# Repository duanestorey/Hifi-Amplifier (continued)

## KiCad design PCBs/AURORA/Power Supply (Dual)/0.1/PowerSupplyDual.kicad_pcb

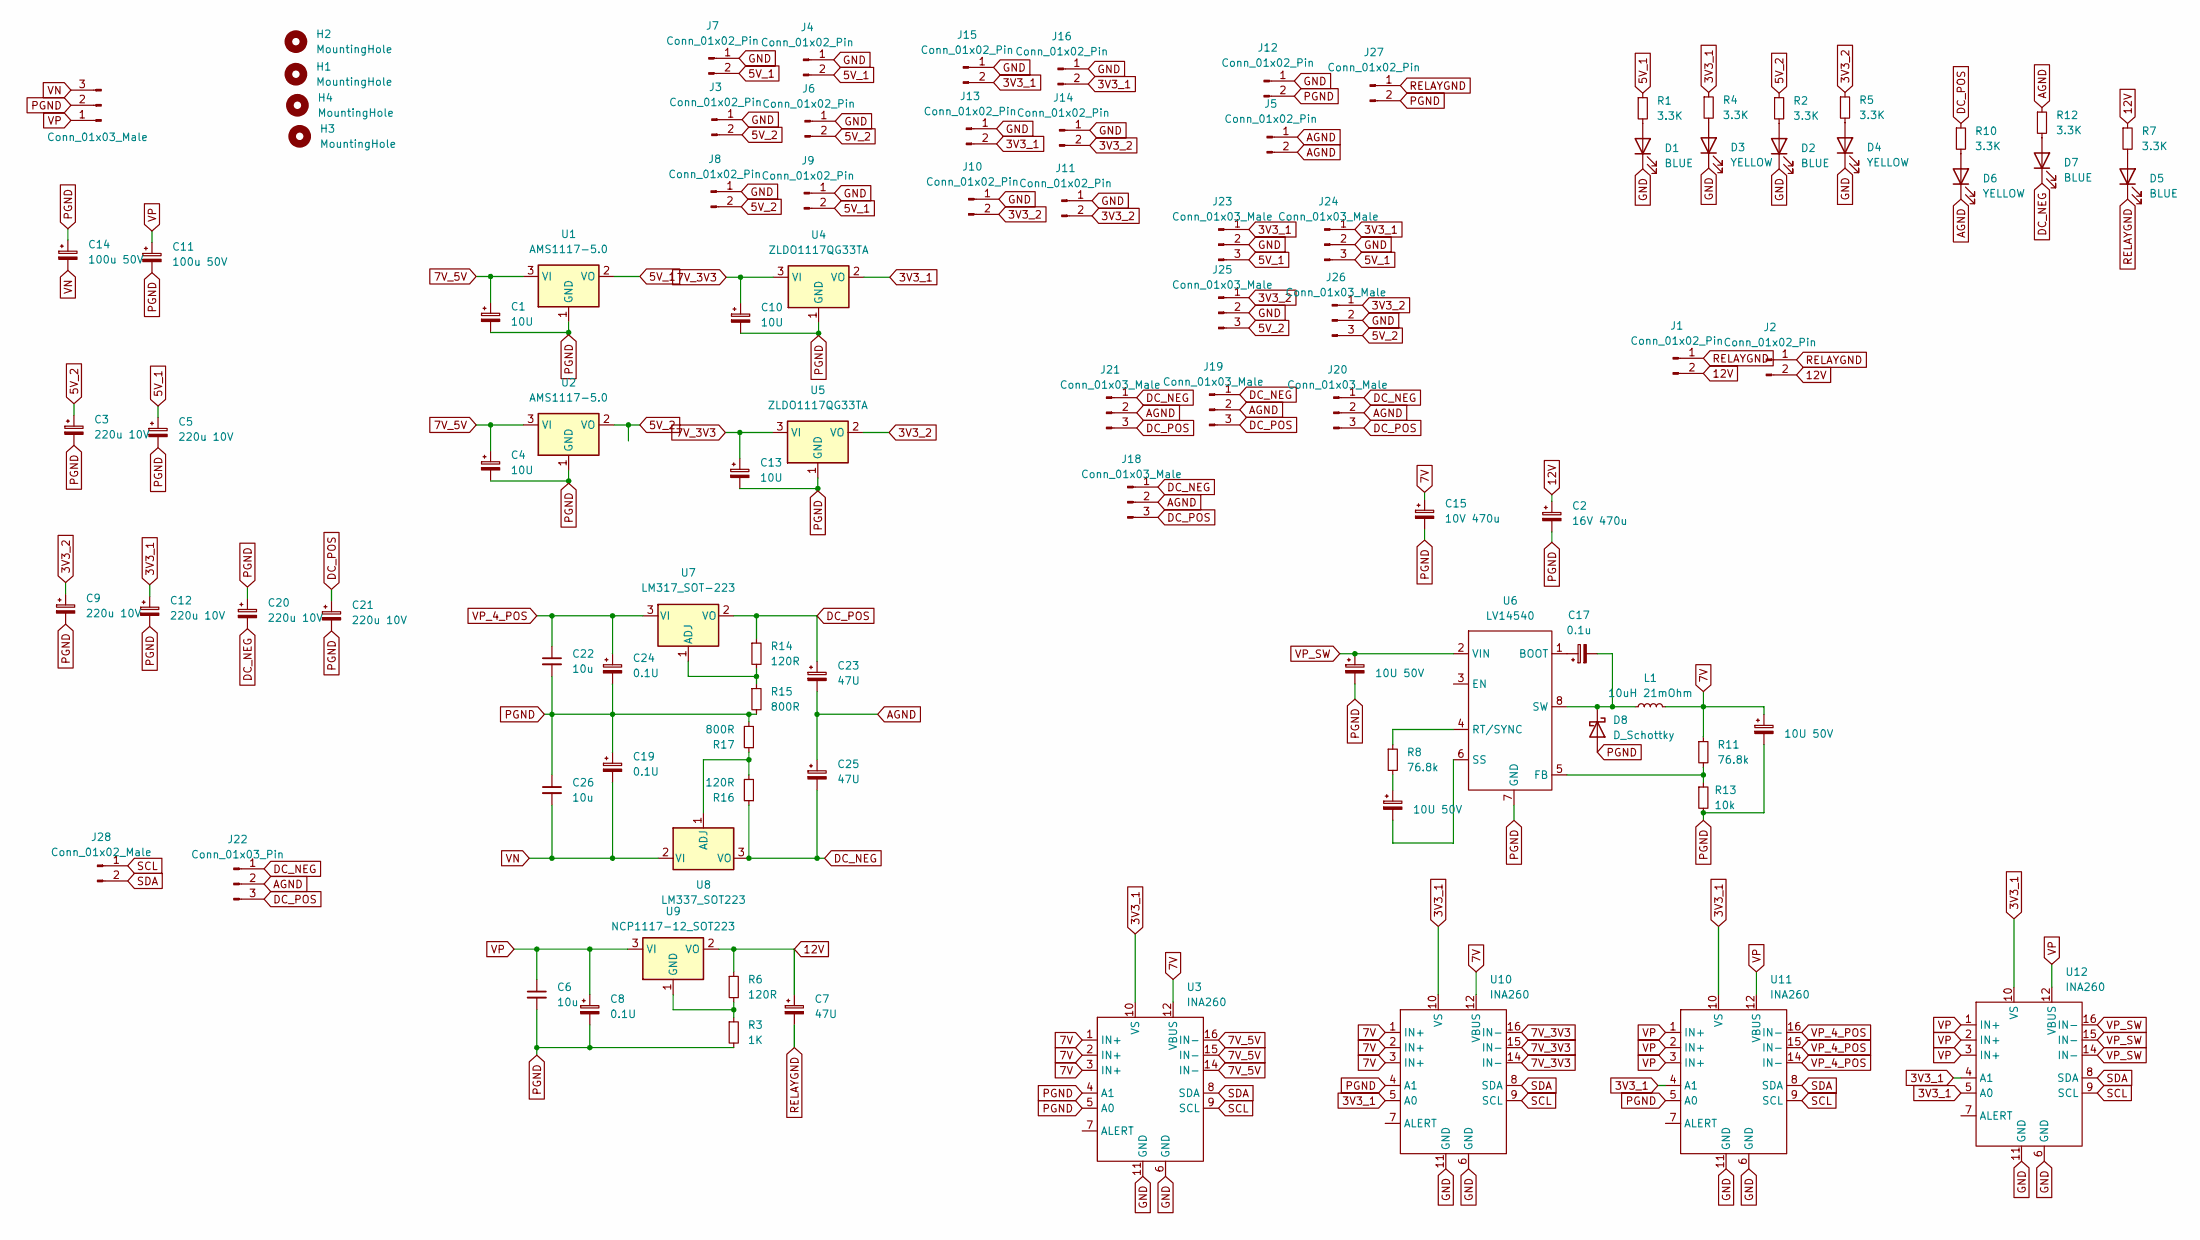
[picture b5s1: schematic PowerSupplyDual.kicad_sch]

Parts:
C1, C4, C10, C13: 10U; C_1206_3216Metric_Pad1.33x1.80mm_HandSolder
C2: 16V 470u; CP_Radial_D8.0mm_P3.50mm
C3, C5, C9, C12, C20, C21: 220u 10V; CP_Radial_D6.3mm_P2.50mm
C6, C22, C26: 10u; C_1206_3216Metric_Pad1.33x1.80mm_HandSolder
C7, C23, C25: 47U; C_1206_3216Metric_Pad1.33x1.80mm_HandSolder
C8, C19, C24: 0.1U; C_0603_1608Metric_Pad1.08x0.95mm_HandSolder
C11, C14: 100u 50V; CP_Radial_D8.0mm_P3.50mm
C15: 10V 470u; CP_Radial_D8.0mm_P3.50mm
C16, C18, C27: 10U 50V; C_1206_3216Metric_Pad1.33x1.80mm_HandSolder
C17: 0.1u; C_0805_2012Metric_Pad1.18x1.45mm_HandSolder
D1, D2, D5, D7: BLUE; LED_0805_2012Metric_Pad1.15x1.40mm_HandSolder
D3, D4, D6: YELLOW; LED_0805_2012Metric_Pad1.15x1.40mm_HandSolder
D8: D_Schottky; D_MELF
H1, H2, H3, H4: MountingHole; MountingHole_3.2mm_M3
J1, J2, J3, J4, J5, J6, J7, J8, J9, J10, J11, J13, J14, J15, J16: Conn_01x02_Pin; JST_PH_B2B-PH-K_1x02_P2.00mm_Vertical
J12, J27: Conn_01x02_Pin; PinHeader_1x02_P2.54mm_Vertical
J17: Conn_01x03_Male; JST_VH_B3P-VH_1x03_P3.96mm_Vertical
J18, J19, J20, J21, J23, J24, J25, J26: Conn_01x03_Male; JST_PH_B3B-PH-K_1x03_P2.00mm_Vertical
J22: Conn_01x03_Pin; PinHeader_1x03_P2.54mm_Vertical
J28: Conn_01x02_Male; JST_PH_B2B-PH-K_1x02_P2.00mm_Vertical
L1: 10uH 21mOhm; L_Bourns_SRR1208_12.7x12.7mm
R1, R2, R4, R5, R7, R10, R12: 3.3K; R_0603_1608Metric_Pad0.98x0.95mm_HandSolder
R3: 1K; R_0603_1608Metric_Pad0.98x0.95mm_HandSolder
R6, R14, R16: 120R; R_0603_1608Metric_Pad0.98x0.95mm_HandSolder
R8, R11: 76.8k; R_0603_1608Metric_Pad0.98x0.95mm_HandSolder
R13: 10k; R_0603_1608Metric_Pad0.98x0.95mm_HandSolder
R15, R17: 800R; R_0603_1608Metric_Pad0.98x0.95mm_HandSolder
U1, U2: AMS1117-5.0; SOT-223-3_TabPin2
U3, U10, U11, U12: INA260; TSSOP-16_4.4x5mm_P0.65mm
U4, U5: ZLDO1117QG33TA; SOT-223-3_TabPin2
U6: LV14540; Texas_R-PDSO-G8_EP2.95x4.9mm_Mask2.4x3.1mm_ThermalVias
U7: LM317_SOT-223; SOT-223-3_TabPin2
U8: LM337_SOT223; SOT-223-3_TabPin2
U9: NCP1117-12_SOT223; SOT-223-3_TabPin2

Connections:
3V3_1: C12.1, J13.2, J15.2, J16.2, J23.1, J24.1, R4.1, U3.10 (VS), U4.2 (VO), U10.5 (A0), U10.10 (VS), U11.4 (A1), U11.10 (VS), U12.4 (A1), U12.5 (A0), U12.10 (VS)
3V3_2: C9.1, J10.2, J11.2, J14.2, J25.1, J26.1, R5.1, U5.2 (VO)
5V_1: C5.1, J4.2, J7.2, J9.2, J23.3, J24.3, R1.1, U1.2 (VO)
5V_2: C3.1, J3.2, J6.2, J8.2, J25.3, J26.3, R2.1, U2.2 (VO)
7V: C15.1, C18.1, L1.2, R11.1, U3.1 (IN+), U3.2 (IN+), U3.3 (IN+), U3.12 (VBUS), U10.1 (IN+), U10.2 (IN+), U10.3 (IN+), U10.12 (VBUS)
7V_3V3: C10.1, C13.1, U4.3 (VI), U5.3 (VI), U10.14 (IN-), U10.15 (IN-), U10.16 (IN-)
7V_5V: C1.1, C4.1, U1.3 (VI), U2.3 (VI), U3.14 (IN-), U3.15 (IN-), U3.16 (IN-)
12V: C2.1, C7.1, J1.2, J2.2, R6.1, R7.1, U9.2 (VO)
AGND: C23.2, C25.1, D6.1 (K), J5.1, J5.2, J18.2, J19.2, J20.2, J21.2, J22.2, R12.1
DC_NEG: C20.2, C25.2, D7.1 (K), J18.1, J19.1, J20.1, J21.1, J22.1, R16.1, U8.3 (VO)
DC_POS: C21.1, C23.1, J18.3, J19.3, J20.3, J21.3, J22.3, R10.1, R14.1, U7.2 (VO)
GND: D1.1 (K), D2.1 (K), D3.1 (K), D4.1 (K), J3.1, J4.1, J6.1, J7.1, J8.1, J9.1, J10.1, J11.1, J12.1, J13.1, J14.1, J15.1, J16.1, J23.2, J24.2, J25.2, J26.2, U3.6 (GND), U3.11 (GND), U10.6 (GND), U10.11 (GND), U11.6 (GND), U11.11 (GND), U12.6 (GND), U12.11 (GND)
unnamed: C27.1, R8.2
unnamed: D1.2 (A), R1.2
unnamed: D2.2 (A), R2.2
unnamed: D3.2 (A), R4.2
unnamed: D4.2 (A), R5.2
unnamed: D5.2 (A), R7.2
unnamed: D6.2 (A), R10.2
unnamed: D7.2 (A), R12.2
unnamed: C17.2, D8.1 (K), L1.1, U6.8 (SW)
unnamed: C17.1, U6.1 (BOOT)
unnamed: R11.2, R13.1, U6.5 (FB)
unnamed: R8.1, U6.4 (RT/SYNC)
unnamed: C27.2, U6.6 (SS)
unnamed: R14.2, R15.1, U7.1 (ADJ)
unnamed: R16.2, R17.1, U8.1 (ADJ)
unnamed: R3.1, R6.2, U9.1 (GND)
PGND: C1.2, C2.2, C3.2, C4.2, C5.2, C6.2, C8.2, C9.2, C10.2, C11.2, C12.2, C13.2, C14.1, C15.2, C16.2, C18.2, C19.1, C20.1, C21.2, C22.2, C24.2, C26.1, D8.2 (A), J12.2, J17.2, J27.2, R3.2, R13.2, R15.2, R17.2, U1.1 (GND), U2.1 (GND), U3.4 (A1), U3.5 (A0), U4.1 (GND), U5.1 (GND), U6.7 (GND), U10.4 (A1), U11.5 (A0)
RELAYGND: C7.2, D5.1 (K), J1.1, J2.1, J27.1
SCL: J28.1, U3.9 (SCL), U10.9 (SCL), U11.9 (SCL), U12.9 (SCL)
SDA: J28.2, U3.8 (SDA), U10.8 (SDA), U11.8 (SDA), U12.8 (SDA)
VN: C14.2, C19.2, C26.2, J17.3, U8.2 (VI)
VP: C6.1, C8.1, C11.1, J17.1, U9.3 (VI), U11.1 (IN+), U11.2 (IN+), U11.3 (IN+), U11.12 (VBUS), U12.1 (IN+), U12.2 (IN+), U12.3 (IN+), U12.12 (VBUS)
VP_4_POS: C22.1, C24.1, U7.3 (VI), U11.14 (IN-), U11.15 (IN-), U11.16 (IN-)
VP_SW: C16.1, U6.2 (VIN), U12.14 (IN-), U12.15 (IN-), U12.16 (IN-)

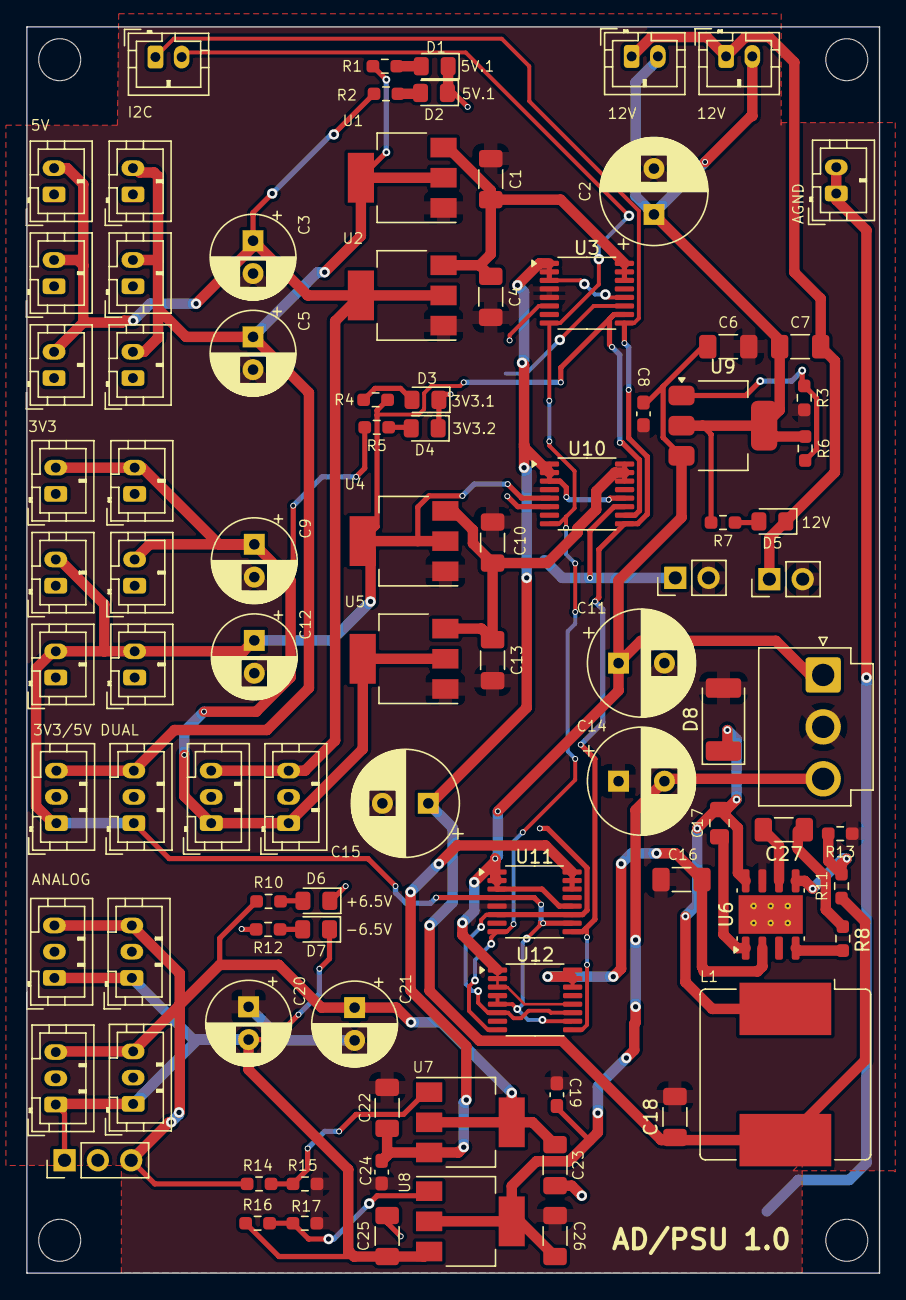
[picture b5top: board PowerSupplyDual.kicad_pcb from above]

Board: 2 copper layers, 65.0 x 95.0 mm, 96 parts (0 on the bottom side), 36 nets.

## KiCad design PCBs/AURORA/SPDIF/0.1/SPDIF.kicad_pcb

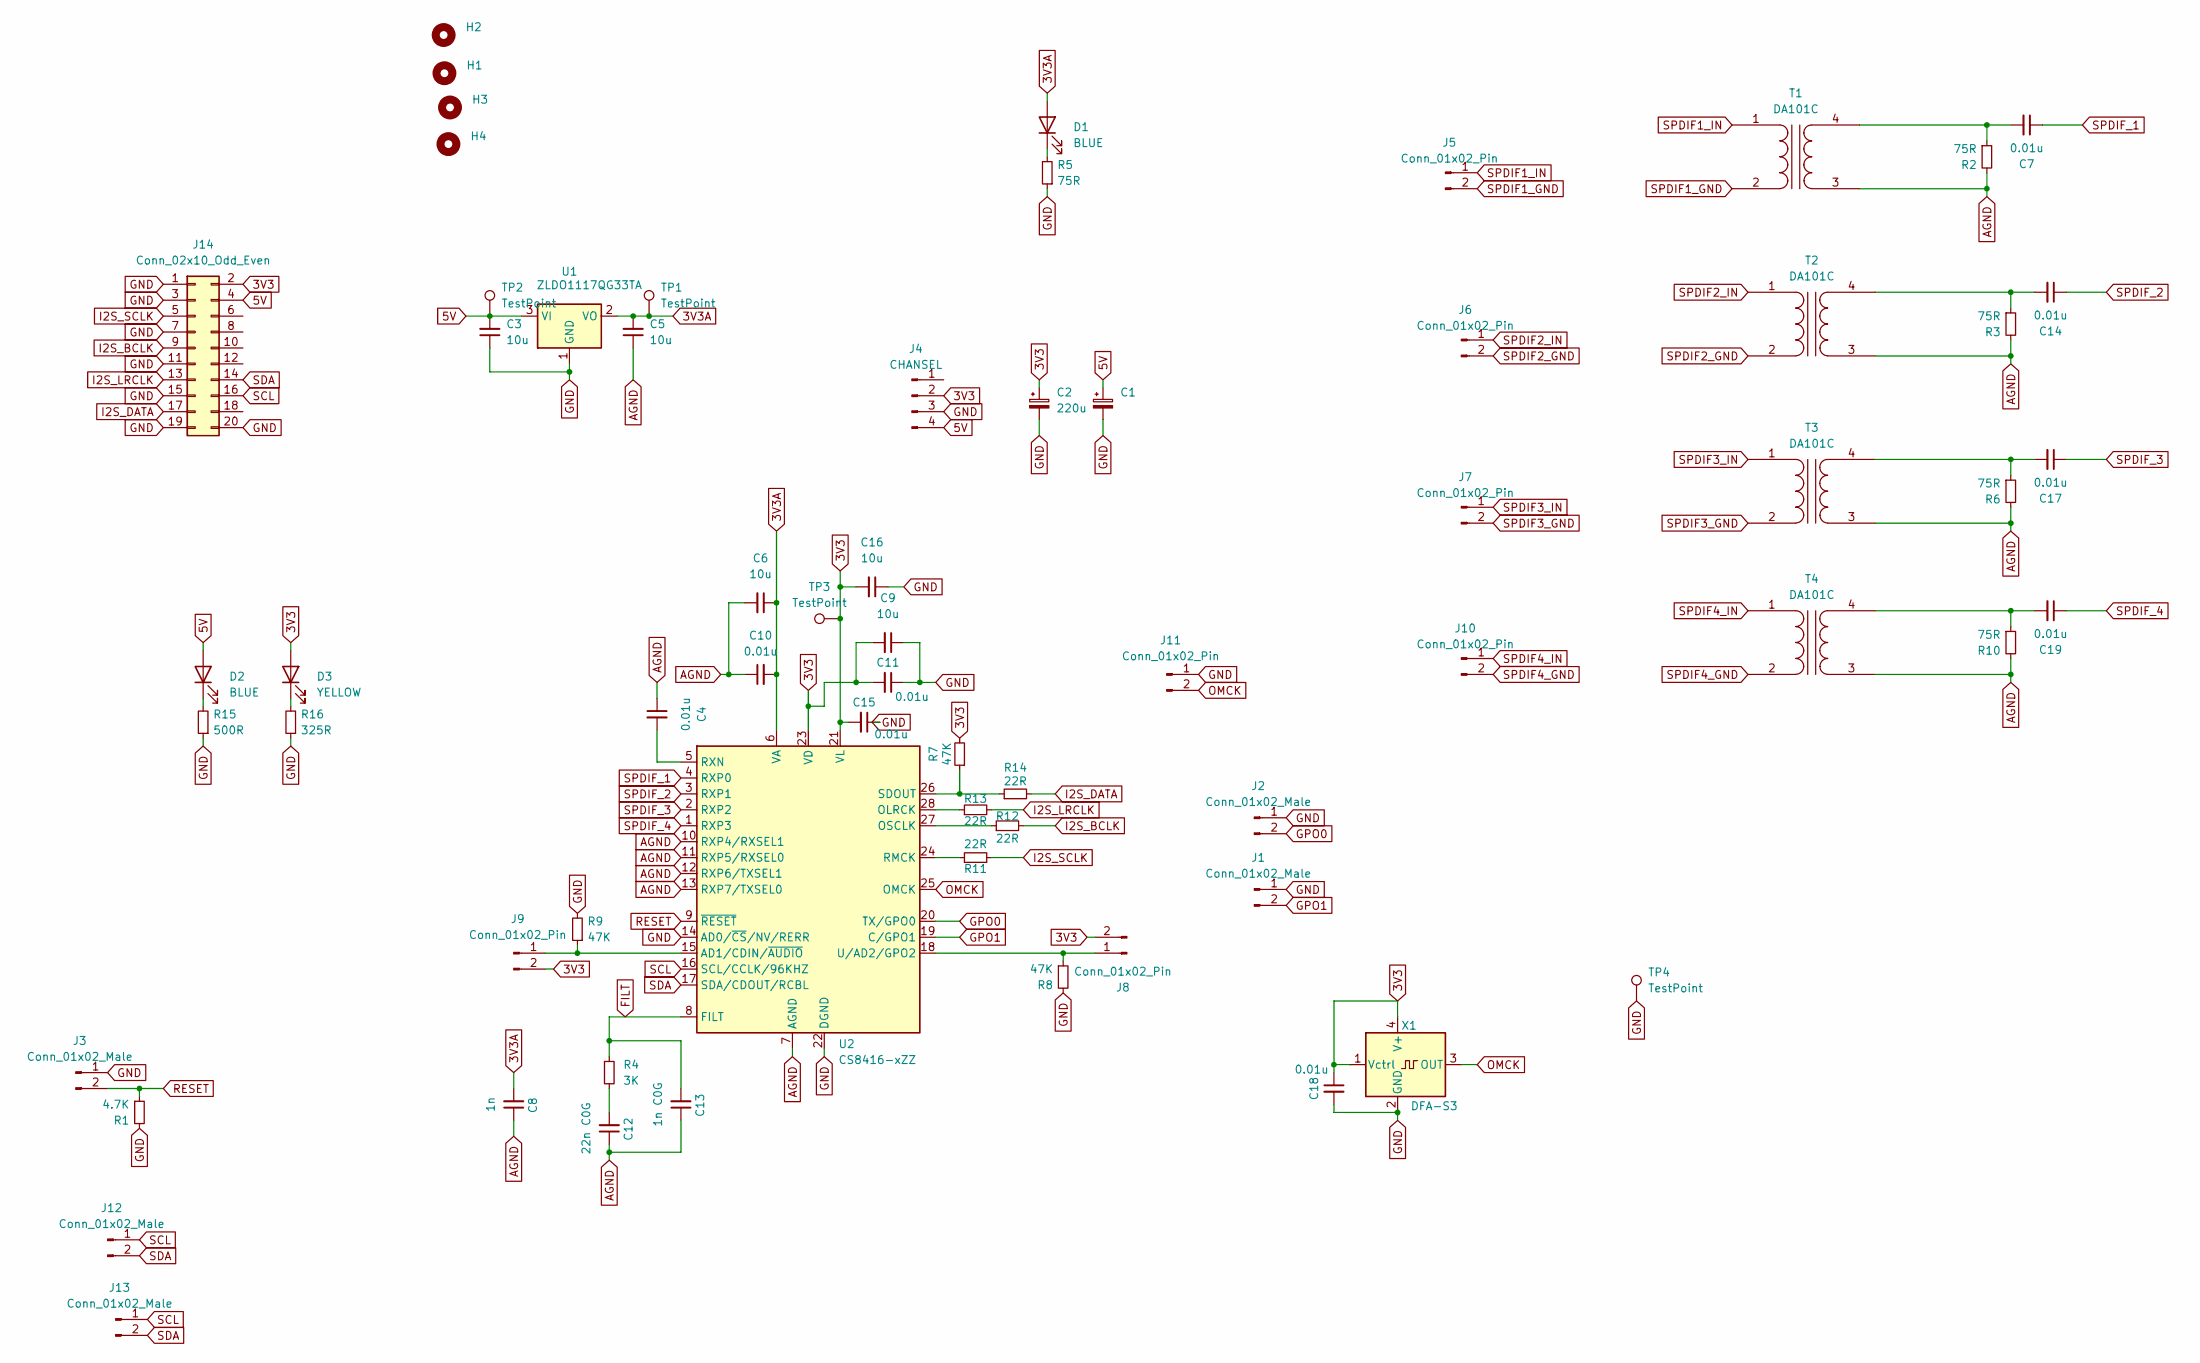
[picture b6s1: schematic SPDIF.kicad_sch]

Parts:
C1, C2: 220u; CP_Radial_D6.3mm_P2.50mm
C3, C5, C6, C9, C16: 10u; C_1206_3216Metric_Pad1.33x1.80mm_HandSolder
C4, C7, C14, C17, C19: 0.01u; C_0805_2012Metric_Pad1.18x1.45mm_HandSolder
C8: 1n; C_0805_2012Metric_Pad1.18x1.45mm_HandSolder
C10: 0.01u; C_1206_3216Metric_Pad1.33x1.80mm_HandSolder
C11, C15, C18: 0.01u; C_0805_2012Metric
C12: 22n C0G; C_0805_2012Metric_Pad1.18x1.45mm_HandSolder
C13: 1n C0G; C_0805_2012Metric_Pad1.18x1.45mm_HandSolder
D1, D2: BLUE; LED_0805_2012Metric_Pad1.15x1.40mm_HandSolder
D3: YELLOW; LED_0805_2012Metric_Pad1.15x1.40mm_HandSolder
H1, H2, H3, H4: MountingHole; MountingHole_3.2mm_M3
J1, J2, J3, J12, J13: Conn_01x02_Male; JST_PH_B2B-PH-K_1x02_P2.00mm_Vertical
J4: CHANSEL; JST_XH_B4B-XH-A_1x04_P2.50mm_Vertical
J5, J6, J7, J10: Conn_01x02_Pin; JST_XH_B2B-XH-A_1x02_P2.50mm_Vertical
J8, J9, J11: Conn_01x02_Pin; PinHeader_1x02_P2.54mm_Vertical
J14: Conn_02x10_Odd_Even; PinHeader_2x10_P2.54mm_Vertical
R1: 4.7K; R_0603_1608Metric_Pad0.98x0.95mm_HandSolder
R2, R3, R5, R6, R10: 75R; R_0603_1608Metric_Pad0.98x0.95mm_HandSolder
R4: 3K; R_0805_2012Metric_Pad1.20x1.40mm_HandSolder
R7, R8, R9: 47K; R_0603_1608Metric_Pad0.98x0.95mm_HandSolder
R11, R12, R13, R14: 22R; R_1206_3216Metric_Pad1.30x1.75mm_HandSolder
R15: 500R; R_0603_1608Metric_Pad0.98x0.95mm_HandSolder
R16: 325R; R_0603_1608Metric_Pad0.98x0.95mm_HandSolder
T1, T2, T3, T4: DA101C
TP1, TP2, TP3, TP4: TestPoint; TestPoint_THTPad_2.0x2.0mm_Drill1.0mm
U1: ZLDO1117QG33TA; SOT-223-3_TabPin2
U2: CS8416-xZZ; TSSOP-28_4.4x9.7mm_P0.65mm
X1: DFA-S3; Oscillator_SMD_EuroQuartz_XO53-4Pin_5.0x3.2mm_HandSoldering

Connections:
3V3: C2.1, C9.2, C11.2, C15.2, C16.2, C18.1, D3.2 (A), J4.2, J8.2, J9.2, J14.2, R7.2, TP3.1, U2.21 (VL), U2.23 (VD), X1.1 (Vctrl), X1.4 (V+)
3V3A: C5.2, C6.1, C8.2, C10.2, D1.2 (A), TP1.1, U1.2 (VO), U2.6 (VA)
5V: C1.1, C3.2, D2.2 (A), J4.4, J14.4, TP2.1, U1.3 (VI)
AGND: C4.1, C5.1, C6.2, C8.1, C10.1, C12.1, C13.1, R2.2, R3.2, R6.2, R10.2, T1.3 (SA), T2.3 (SA), T3.3 (SA), T4.3 (SA), U2.7 (AGND), U2.10 (RXP4/RXSEL1), U2.11 (RXP5/RXSEL0), U2.12 (RXP6/TXSEL1), U2.13 (RXP7/TXSEL0)
FILT: C13.2, R4.1, U2.8 (FILT)
GND: C1.2, C2.2, C3.1, C9.1, C11.1, C15.1, C16.1, C18.2, J1.1, J2.1, J3.1, J4.3, J11.1, J14.1, J14.3, J14.7, J14.11, J14.15, J14.19, J14.20, R1.2, R5.1, R8.2, R9.2, R15.1, R16.1, TP4.1, U1.1 (GND), U2.14 (AD0/~CS/NV/RERR), U2.22 (DGND), X1.2 (GND)
GPO0: J2.2, U2.20 (TX/GPO0)
GPO1: J1.2, U2.19 (C/GPO1)
I2S_BCLK: J14.9, R12.2
I2S_DATA: J14.17, R14.2
I2S_LRCLK: J14.13, R13.2
I2S_SCLK: J14.5, R11.2
unnamed: C12.2, R4.2
unnamed: D1.1 (K), R5.2
unnamed: D2.1 (K), R15.2
unnamed: D3.1 (K), R16.2
unnamed: J8.1, R8.1, U2.18 (U/AD2/GPO2)
unnamed: J9.1, R9.1, U2.15 (AD1/CDIN/~AUDIO)
unnamed: C7.2, R2.1, T1.4 (SB)
unnamed: C14.2, R3.1, T2.4 (SB)
unnamed: C17.2, R6.1, T3.4 (SB)
unnamed: C19.2, R10.1, T4.4 (SB)
unnamed: R13.1, U2.28 (OLRCK)
unnamed: R12.1, U2.27 (OSCLK)
unnamed: R11.1, U2.24 (RMCK)
unnamed: C4.2, U2.5 (RXN)
unnamed: R7.1, R14.1, U2.26 (SDOUT)
OMCK: J11.2, U2.25 (OMCK), X1.3 (OUT)
RESET: J3.2, R1.1, U2.9 (~RESET)
SCL: J12.1, J13.1, J14.16, U2.16 (SCL/CCLK/96KHZ)
SDA: J12.2, J13.2, J14.14, U2.17 (SDA/CDOUT/RCBL)
SPDIF1_GND: J5.2, T1.2 (AB)
SPDIF1_IN: J5.1, T1.1 (AA)
SPDIF2_GND: J6.2, T2.2 (AB)
SPDIF2_IN: J6.1, T2.1 (AA)
SPDIF3_GND: J7.2, T3.2 (AB)
SPDIF3_IN: J7.1, T3.1 (AA)
SPDIF4_GND: J10.2, T4.2 (AB)
SPDIF4_IN: J10.1, T4.1 (AA)
SPDIF_1: C7.1, U2.4 (RXP0)
SPDIF_2: C14.1, U2.3 (RXP1)
SPDIF_3: C17.1, U2.2 (RXP2)
SPDIF_4: C19.1, U2.1 (RXP3)

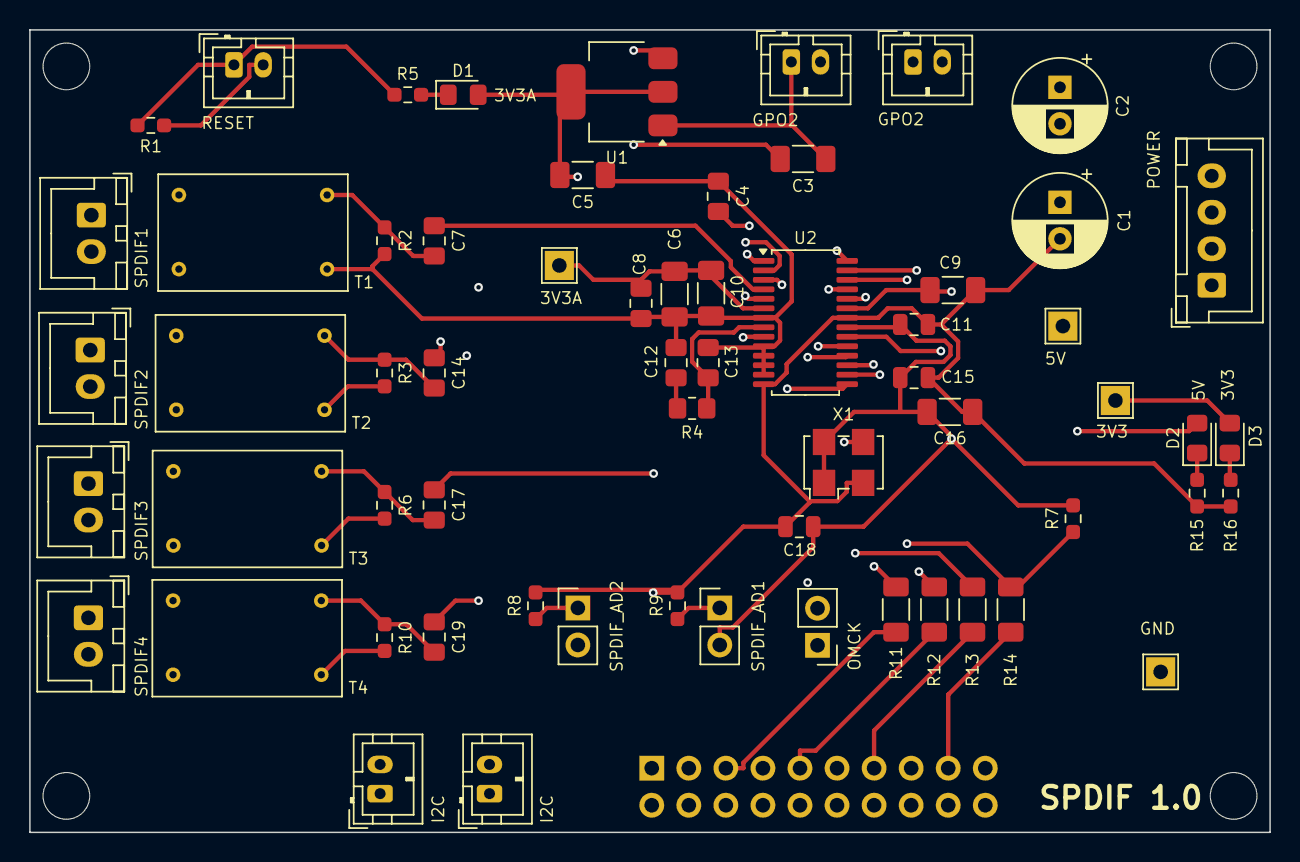
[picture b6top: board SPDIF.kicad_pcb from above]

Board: 4 copper layers, 85.0 x 55.0 mm, 67 parts (1 on the bottom side), 43 nets.
